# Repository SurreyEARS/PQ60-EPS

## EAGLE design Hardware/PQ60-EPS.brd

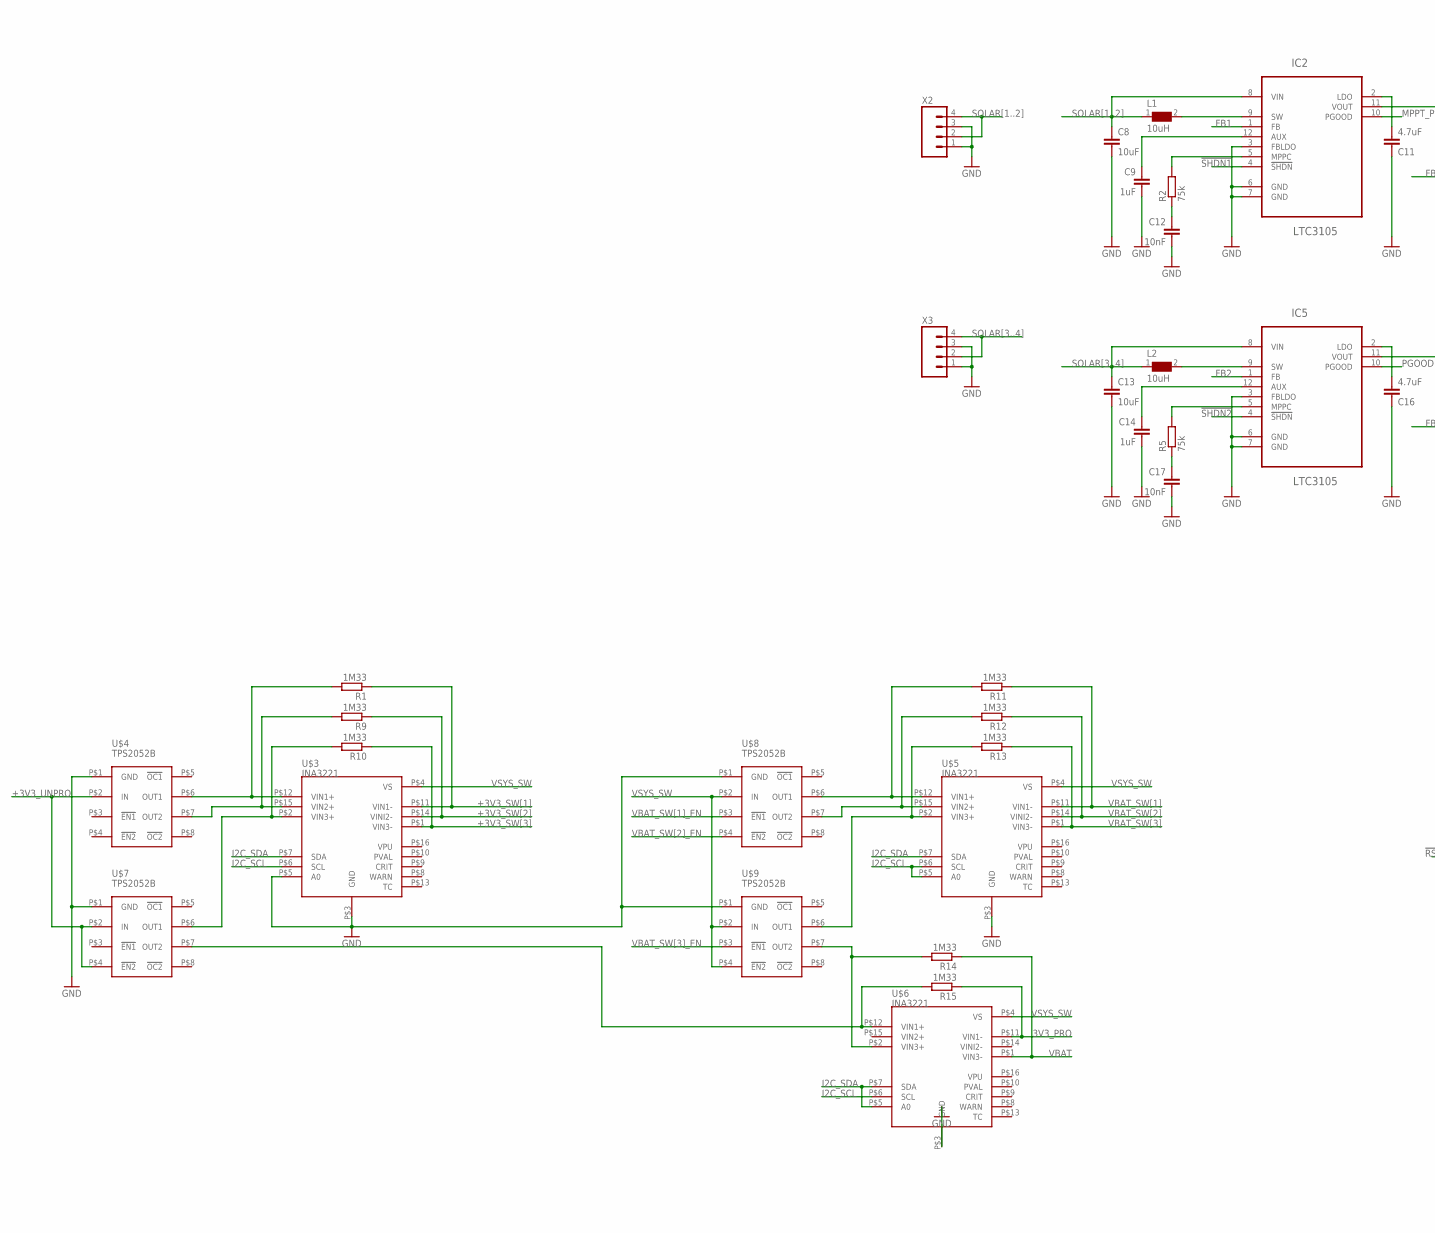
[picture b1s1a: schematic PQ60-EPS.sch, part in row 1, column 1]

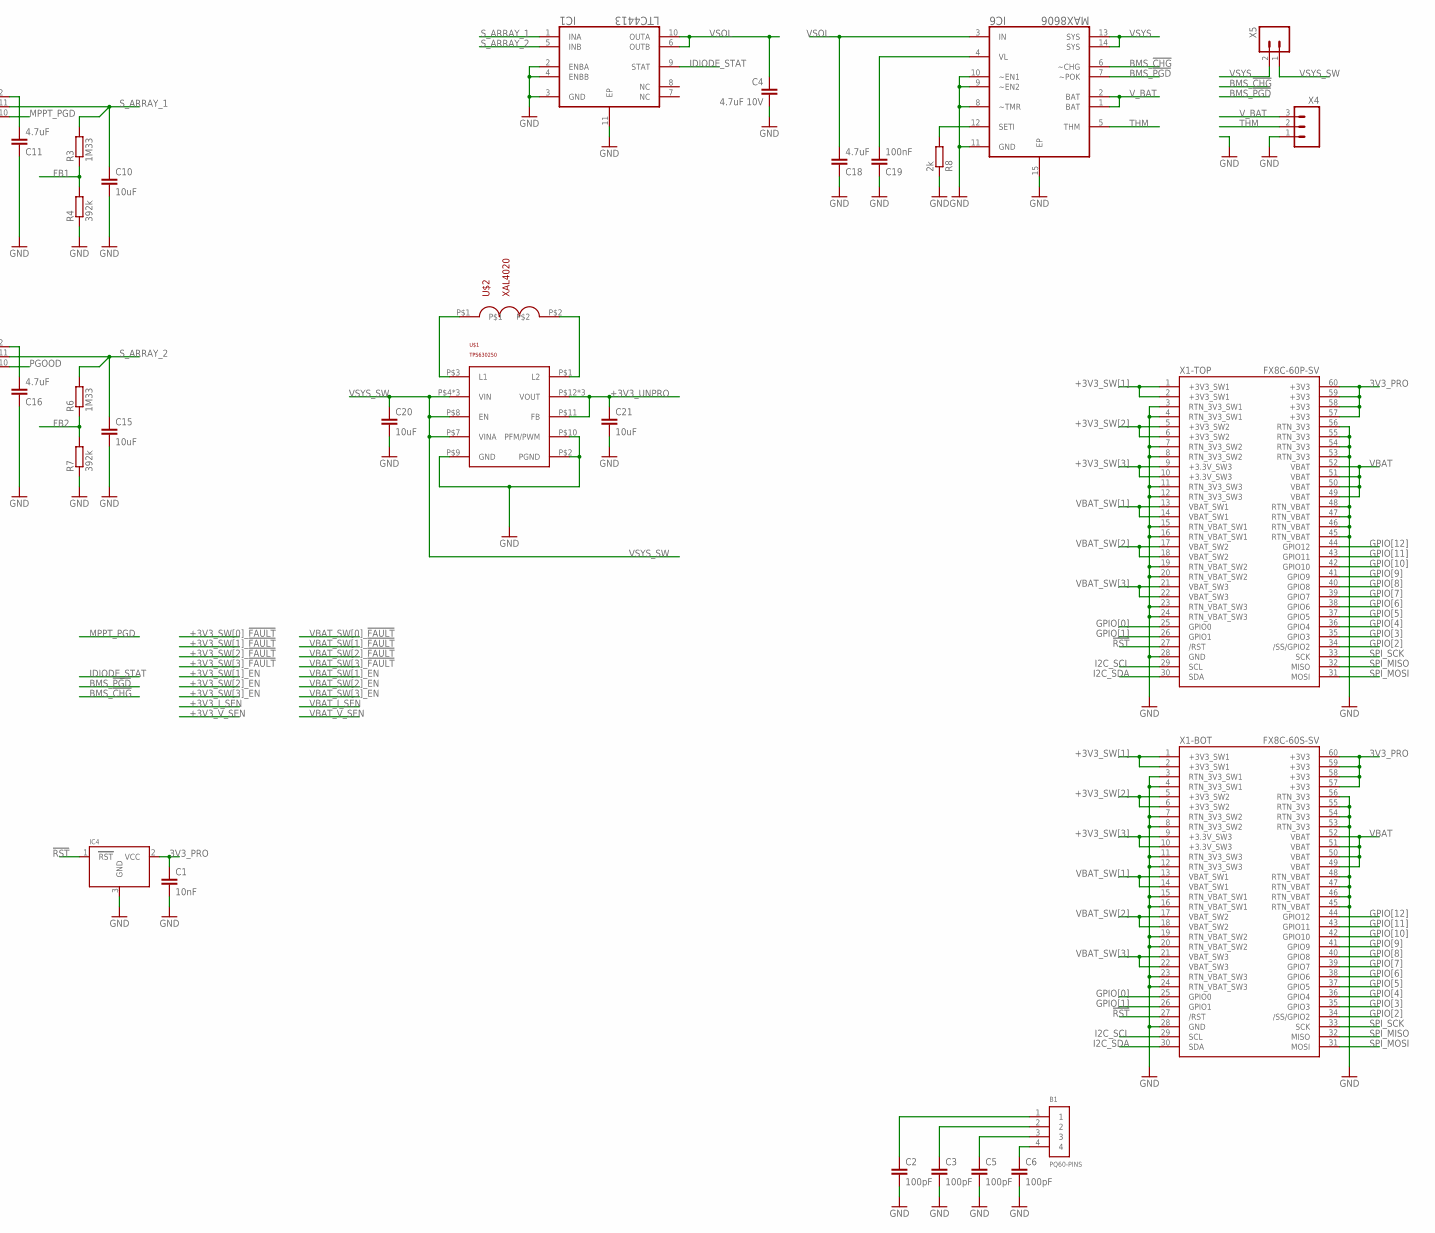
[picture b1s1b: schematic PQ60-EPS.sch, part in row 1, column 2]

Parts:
B1: PQ60-PINS; PQ60_PINS
C1, C12, C17: 10nF; C0603
C2, C3, C5, C6: 100pF; C0402; MPN 02013A101JAT2A
C4: 4.7uF 10V; C0805
C8, C10, C13, C15, C20, C21: 10uF; C0603
C9, C14: 1uF; C0603; MPN 02016D105MAT2A
C11, C16, C18: 4.7uF; C0603
C19: 100nF; C0603
IC1: LTC4413; DFN300X300X80-11N
IC2, IC5: LTC3105; SOP65P490X110-12N
IC4: MCP130TREFLOW; SOT23-R
IC6: MAX8606; DFN300X300X80-15N
L1, L2: 10uH; WE-TPC_3816; MPN 744031100
R1, R3, R6, R9, R10, R11, R12, R13, R14, R15: 1M33; R0603
R2, R5: 75k; R0603
R4, R7: 392k; R0603
R8: 2k; R0603
U$1: TPS630250; VQFN14
U$2: XAL4020
U$3, U$5, U$6: INA3221; VQFN16
U$4, U$7, U$8, U$9: TPS2052B; 8SON
X1-BOT: FX8C-60S-SV
X1-TOP: FX8C-60P-SV
X2, X3: M04SMD2; 1X04-1MM-RA
X4: M03SMD; 1X03-1MM-RA
X5: M02SMD; 1X02-1MM-RA

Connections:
3V3_PRO: C1.1, IC4.2 (VCC), R15.1, U$6.P$11 (VIN1-), X1-BOT.57 (+3V3), X1-BOT.58 (+3V3), X1-BOT.59 (+3V3), X1-BOT.60 (+3V3), X1-TOP.57 (+3V3), X1-TOP.58 (+3V3), X1-TOP.59 (+3V3), X1-TOP.60 (+3V3)
!RST: IC4.1 (RST), X1-BOT.27 (/RST), X1-TOP.27 (/RST)
!SHDN1!: IC2.4 (!SHDN!)
!SHDN2!: IC5.4 (!SHDN!)
+3V3_SW[1]: R1.1, U$3.P$11 (VIN1-), X1-BOT.1 (+3V3_SW1), X1-BOT.2 (+3V3_SW1), X1-TOP.1 (+3V3_SW1), X1-TOP.2 (+3V3_SW1)
+3V3_SW[2]: R9.1, U$3.P$14 (VINI2-), X1-BOT.5 (+3V3_SW2), X1-BOT.6 (+3V3_SW2), X1-TOP.5 (+3V3_SW2), X1-TOP.6 (+3V3_SW2)
+3V3_SW[3]: R10.1, U$3.P$1 (VIN3-), X1-BOT.9 (+3.3V_SW3), X1-BOT.10 (+3.3V_SW3), X1-TOP.9 (+3.3V_SW3), X1-TOP.10 (+3.3V_SW3)
+3V3_UNPRO: C21.1, U$1.P$11 (FB), U$1.P$12 (VOUT), U$1.P$13 (VOUT), U$1.P$14 (VOUT), U$4.P$2 (IN), U$7.P$2 (IN), U$7.P$4 (!EN2!)
AUX1: C9.1, IC2.12 (AUX)
AUX2: C14.1, IC5.12 (AUX)
BATT_PROG: IC6.12 (SETI), R8.2
BMS_!CHG!: IC6.6 (~CHG)
BMS_!PGD!: IC6.7 (~POK)
FB1: IC2.1 (FB), R3.1, R4.2
FB2: IC5.1 (FB), R6.1, R7.2
GND: C1.2, C2.2, C3.2, C4.2, C5.2, C6.2, C8.2, C9.2, C10.2, C11.1, C12.2, C13.2, C14.2, C15.2, C16.1, C17.2, C18.1, C19.1, C20.2, C21.2, IC1.2 (ENBA), IC1.3 (GND), IC1.4 (ENBB), IC1.11 (EP), IC2.3 (FBLDO), IC2.6 (GND), IC2.7 (GND), IC4.3 (GND), IC5.3 (FBLDO), IC5.6 (GND), IC5.7 (GND), IC6.8 (~TMR), IC6.9 (~EN2), IC6.10 (~EN1), IC6.11 (GND), IC6.15 (EP), R4.1, R7.1, R8.1, U$1.P$2 (PGND), U$1.P$9 (GND), U$1.P$10 (PFM/PWM), U$3.P$3 (GND), U$3.P$5 (A0), U$4.P$1 (GND), U$5.P$3 (GND), U$6.P$3 (GND), U$7.P$1 (GND), U$8.P$1 (GND), U$9.P$1 (GND), X1-BOT.3 (RTN_3V3_SW1), X1-BOT.4 (RTN_3V3_SW1), X1-BOT.7 (RTN_3V3_SW2), X1-BOT.8 (RTN_3V3_SW2), X1-BOT.11 (RTN_3V3_SW3), X1-BOT.12 (RTN_3V3_SW3), X1-BOT.15 (RTN_VBAT_SW1), X1-BOT.16 (RTN_VBAT_SW1), X1-BOT.19 (RTN_VBAT_SW2), X1-BOT.20 (RTN_VBAT_SW2), X1-BOT.23 (RTN_VBAT_SW3), X1-BOT.24 (RTN_VBAT_SW3), X1-BOT.28 (GND), X1-BOT.45 (RTN_VBAT), X1-BOT.46 (RTN_VBAT), X1-BOT.47 (RTN_VBAT), X1-BOT.48 (RTN_VBAT), X1-BOT.53 (RTN_3V3), X1-BOT.54 (RTN_3V3), X1-BOT.55 (RTN_3V3), X1-BOT.56 (RTN_3V3), X1-TOP.3 (RTN_3V3_SW1), X1-TOP.4 (RTN_3V3_SW1), X1-TOP.7 (RTN_3V3_SW2), X1-TOP.8 (RTN_3V3_SW2), X1-TOP.11 (RTN_3V3_SW3), X1-TOP.12 (RTN_3V3_SW3), X1-TOP.15 (RTN_VBAT_SW1), X1-TOP.16 (RTN_VBAT_SW1), X1-TOP.19 (RTN_VBAT_SW2), X1-TOP.20 (RTN_VBAT_SW2), X1-TOP.23 (RTN_VBAT_SW3), X1-TOP.24 (RTN_VBAT_SW3), X1-TOP.28 (GND), X1-TOP.45 (RTN_VBAT), X1-TOP.46 (RTN_VBAT), X1-TOP.47 (RTN_VBAT), X1-TOP.48 (RTN_VBAT), X1-TOP.53 (RTN_3V3), X1-TOP.54 (RTN_3V3), X1-TOP.55 (RTN_3V3), X1-TOP.56 (RTN_3V3), X2.1, X2.3, X3.1, X3.3, X4.1
GPIO[0]: X1-BOT.25 (GPIO0), X1-TOP.25 (GPIO0)
GPIO[1]: X1-BOT.26 (GPIO1), X1-TOP.26 (GPIO1)
GPIO[2]: X1-BOT.34 (/SS/GPIO2), X1-TOP.34 (/SS/GPIO2)
GPIO[3]: X1-BOT.35 (GPIO3), X1-TOP.35 (GPIO3)
GPIO[4]: X1-BOT.36 (GPIO4), X1-TOP.36 (GPIO4)
GPIO[5]: X1-BOT.37 (GPIO5), X1-TOP.37 (GPIO5)
GPIO[6]: X1-BOT.38 (GPIO6), X1-TOP.38 (GPIO6)
GPIO[7]: X1-BOT.39 (GPIO7), X1-TOP.39 (GPIO7)
GPIO[8]: X1-BOT.40 (GPIO8), X1-TOP.40 (GPIO8)
GPIO[9]: X1-BOT.41 (GPIO9), X1-TOP.41 (GPIO9)
GPIO[10]: X1-BOT.42 (GPIO10), X1-TOP.42 (GPIO10)
GPIO[11]: X1-BOT.43 (GPIO11), X1-TOP.43 (GPIO11)
GPIO[12]: X1-BOT.44 (GPIO12), X1-TOP.44 (GPIO12)
I2C_SCL: U$3.P$6 (SCL), U$5.P$5 (A0), U$5.P$6 (SCL), U$6.P$6 (SCL), X1-BOT.29 (SCL), X1-TOP.29 (SCL)
I2C_SDA: U$3.P$7 (SDA), U$5.P$7 (SDA), U$6.P$5 (A0), U$6.P$7 (SDA), X1-BOT.30 (SDA), X1-TOP.30 (SDA)
IDIODE_STAT: IC1.9 (STAT)
L1: U$1.P$3 (L1), U$2.P$1
L2: U$1.P$1 (L2), U$2.P$2
LDO1: C11.2, IC2.2 (LDO)
LDO2: C16.2, IC5.2 (LDO)
MPPC1: IC2.5 (MPPC), R2.2
MPPC2: IC5.5 (MPPC), R5.2
MPPT_PGD: IC2.10 (PGOOD)
unnamed: B1.1, C2.1
unnamed: B1.2, C3.1
unnamed: B1.3, C5.1
unnamed: B1.4, C6.1
unnamed: R1.2, U$3.P$12 (VIN1+), U$4.P$6 (OUT1)
unnamed: R9.2, U$3.P$15 (VIN2+), U$4.P$7 (OUT2)
unnamed: R10.2, U$3.P$2 (VIN3+), U$7.P$6 (OUT1)
unnamed: R11.2, U$5.P$12 (VIN1+), U$8.P$6 (OUT1)
unnamed: R12.2, U$5.P$15 (VIN2+), U$8.P$7 (OUT2)
unnamed: R13.2, U$5.P$2 (VIN3+), U$9.P$6 (OUT1)
unnamed: R14.2, U$6.P$2 (VIN3+), U$9.P$7 (OUT2)
unnamed: R15.2, U$6.P$12 (VIN1+), U$7.P$7 (OUT2)
PGOOD: IC5.10 (PGOOD)
SOLAR[1..2]: C8.1, IC2.8 (VIN), L1.1, X2.2, X2.4
SOLAR[3..4]: C13.1, IC5.8 (VIN), L2.1, X3.2, X3.4
SPI_MISO: X1-BOT.32 (MISO), X1-TOP.32 (MISO)
SPI_MOSI: X1-BOT.31 (MOSI), X1-TOP.31 (MOSI)
SPI_SCK: X1-BOT.33 (SCK), X1-TOP.33 (SCK)
SW1: IC2.9 (SW), L1.2
SW2: IC5.9 (SW), L2.2
S_ARRAY_1: C10.1, IC1.1 (INA), IC2.11 (VOUT), R3.2
S_ARRAY_2: C15.1, IC1.5 (INB), IC5.11 (VOUT), R6.2
THM: IC6.5 (THM), X4.2
THM1: C12.1, R2.1
THM2: C17.1, R5.1
VBAT: R14.1, U$6.P$1 (VIN3-), X1-BOT.49 (VBAT), X1-BOT.50 (VBAT), X1-BOT.51 (VBAT), X1-BOT.52 (VBAT), X1-TOP.49 (VBAT), X1-TOP.50 (VBAT), X1-TOP.51 (VBAT), X1-TOP.52 (VBAT)
VBAT_SW[1]: R11.1, U$5.P$11 (VIN1-), X1-BOT.13 (VBAT_SW1), X1-BOT.14 (VBAT_SW1), X1-TOP.13 (VBAT_SW1), X1-TOP.14 (VBAT_SW1)
VBAT_SW[1]_EN: U$8.P$3 (!EN1!)
VBAT_SW[2]: R12.1, U$5.P$14 (VINI2-), X1-BOT.17 (VBAT_SW2), X1-BOT.18 (VBAT_SW2), X1-TOP.17 (VBAT_SW2), X1-TOP.18 (VBAT_SW2)
VBAT_SW[2]_EN: U$8.P$4 (!EN2!)
VBAT_SW[3]: R13.1, U$5.P$1 (VIN3-), X1-BOT.21 (VBAT_SW3), X1-BOT.22 (VBAT_SW3), X1-TOP.21 (VBAT_SW3), X1-TOP.22 (VBAT_SW3)
VBAT_SW[3]_EN: U$9.P$3 (!EN1!)
VL: C19.2, IC6.4 (VL)
VSOL: C4.1, C18.2, IC1.6 (OUTB), IC1.10 (OUTA), IC6.3 (IN)
VSYS: IC6.13 (SYS), IC6.14 (SYS), X5.2
VSYS_SW: C20.1, U$1.P$4 (VIN), U$1.P$5 (VIN), U$1.P$6 (VIN), U$1.P$7 (VINA), U$1.P$8 (EN), U$3.P$4 (VS), U$5.P$4 (VS), U$6.P$4 (VS), U$8.P$2 (IN), U$9.P$2 (IN), U$9.P$4 (!EN2!), X5.1
V_BAT: IC6.1 (BAT), IC6.2 (BAT), X4.3

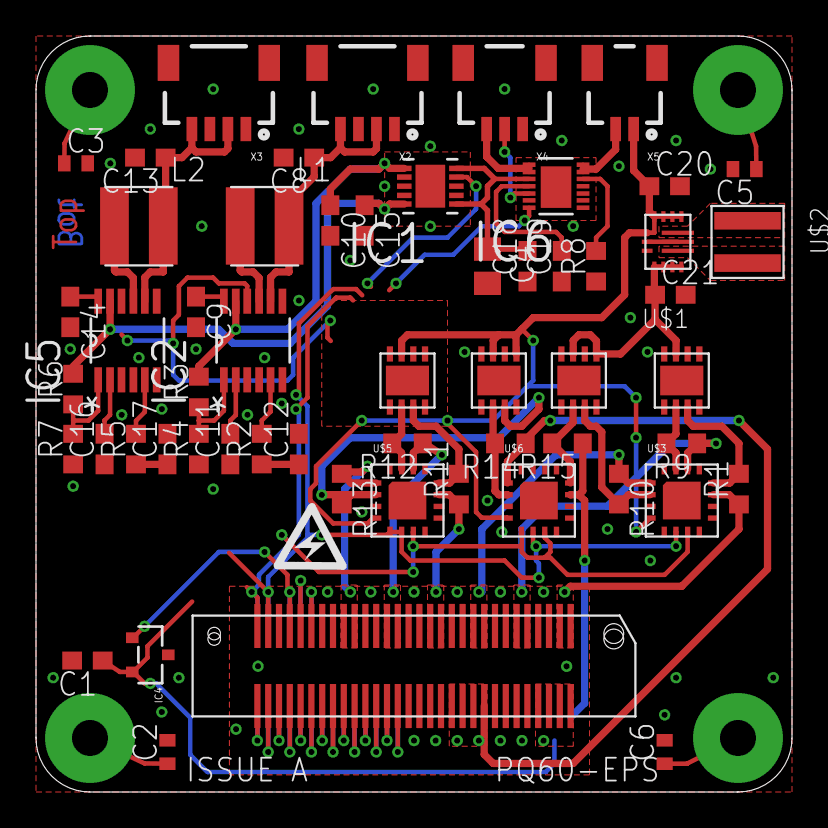
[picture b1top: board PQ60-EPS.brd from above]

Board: 2 copper layers, 42.0 x 42.0 mm, 58 parts (1 on the bottom side), 66 nets.

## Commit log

2015-08-02 Broken out some modules. Swapping SMPS.
2015-08-05 pre deleting prot modules
2015-08-06 routed most of the power

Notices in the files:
parts and their libraries:
SparkFun-Connectors: Licensing: Creative Commons ShareAlike 4.0 International - https://creativecommons.org/licenses/by-sa/4.0
